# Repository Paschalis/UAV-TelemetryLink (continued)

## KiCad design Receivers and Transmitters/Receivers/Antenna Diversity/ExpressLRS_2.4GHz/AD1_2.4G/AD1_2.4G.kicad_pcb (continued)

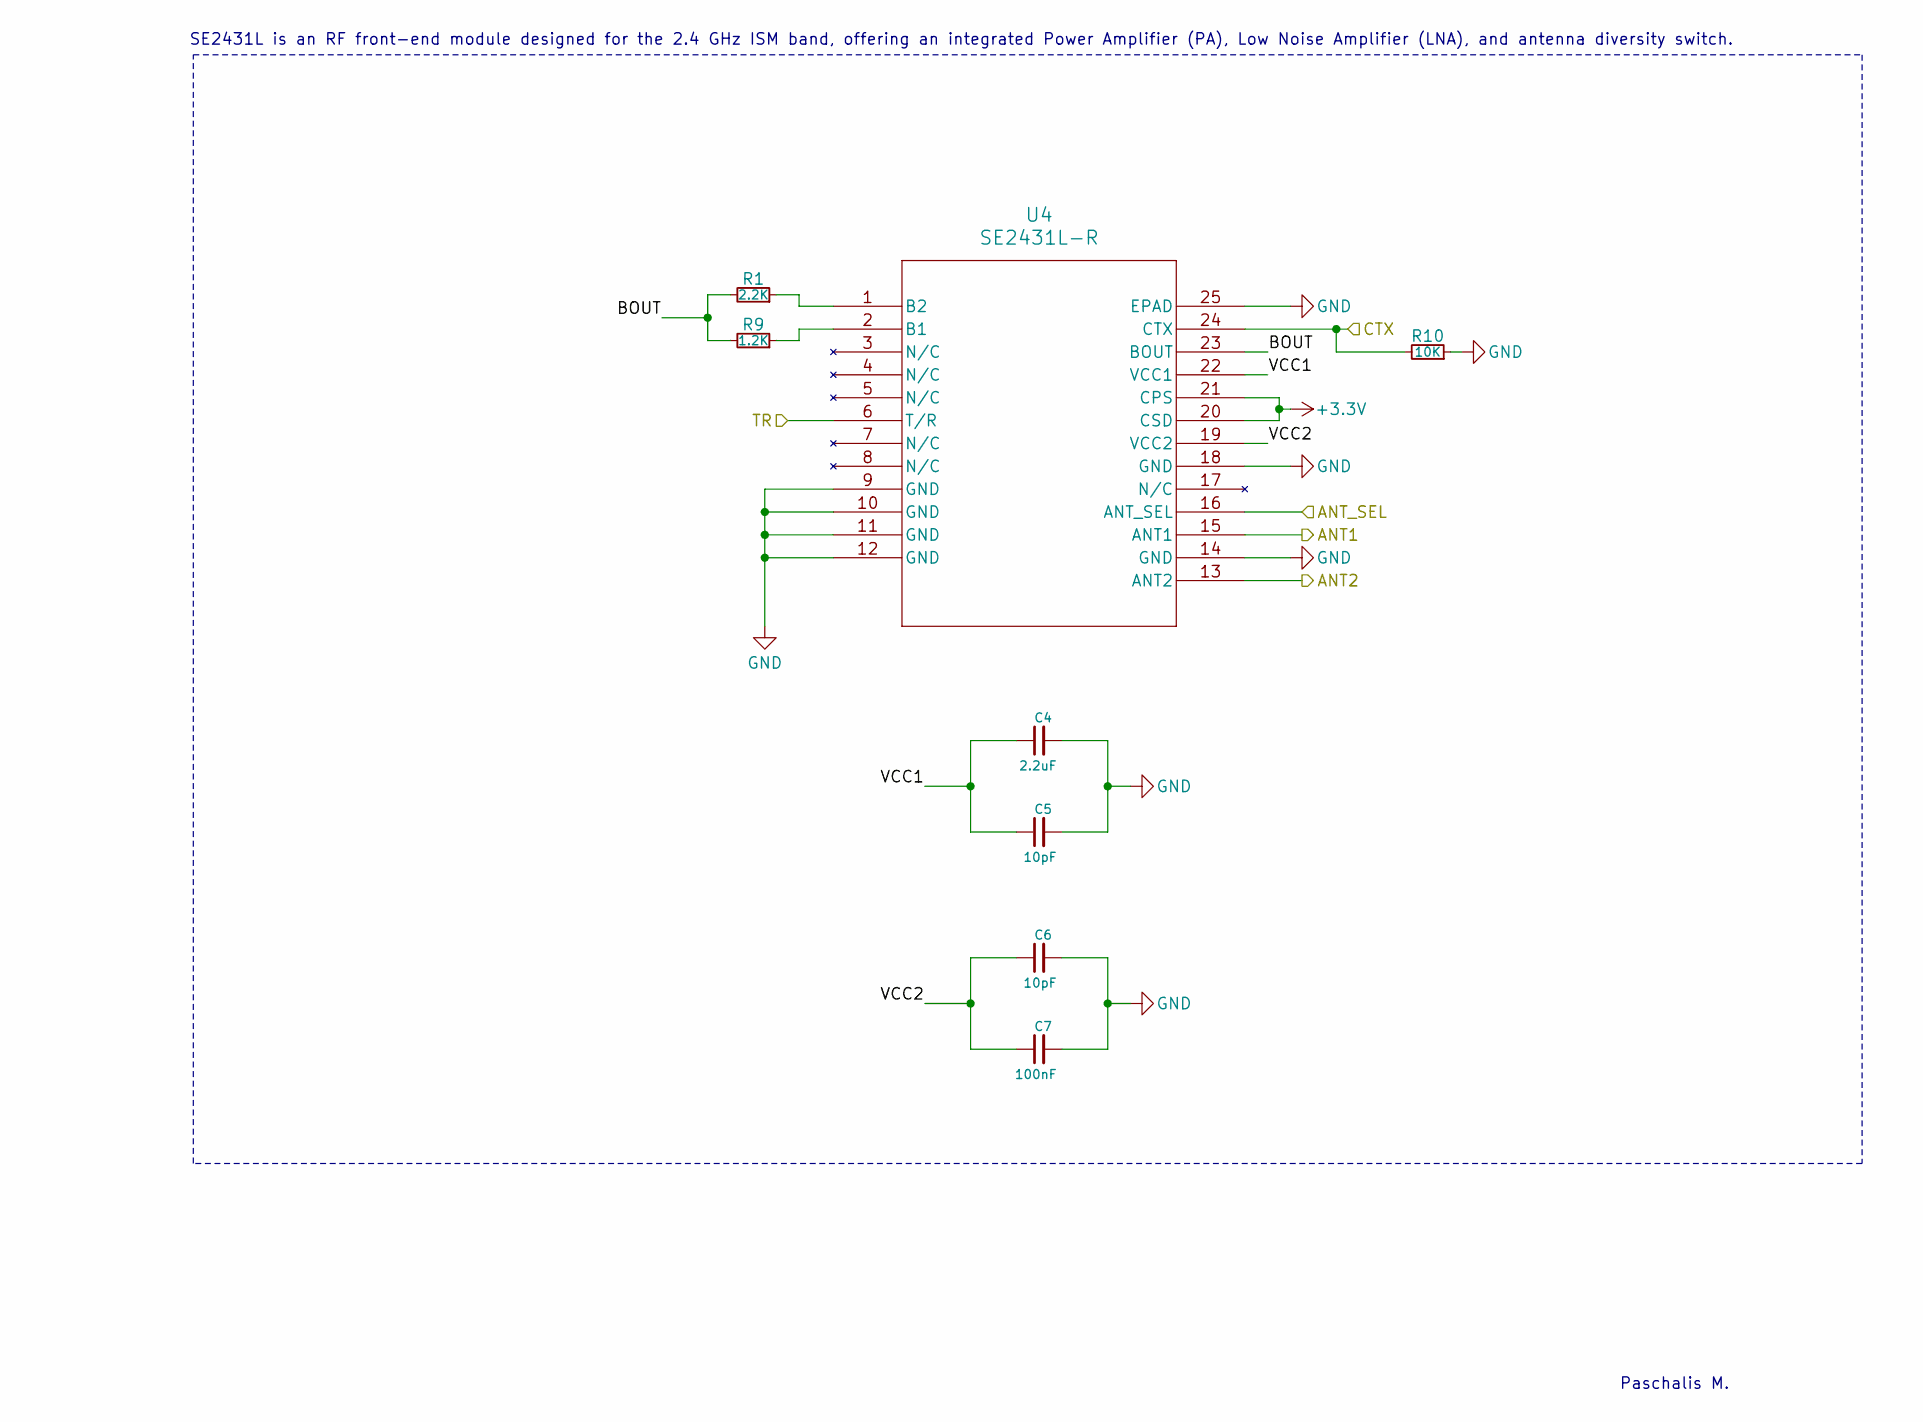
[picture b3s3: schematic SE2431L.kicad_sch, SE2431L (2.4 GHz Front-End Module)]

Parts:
C4: 2.2uF; C_0603_1608Metric_Pad1.08x0.95mm_HandSolder
C5, C6: 10pF; C_0603_1608Metric_Pad1.08x0.95mm_HandSolder
C7: 100nF; C_0603_1608Metric_Pad1.08x0.95mm_HandSolder
R1: 2.2K; R_0603_1608Metric_Pad0.98x0.95mm_HandSolder
R9: 1.2K; R_0603_1608Metric_Pad0.98x0.95mm_HandSolder
R10: 10K; R_0603_1608Metric_Pad0.98x0.95mm_HandSolder
U4: SE2431L-R; SE2431L_SKY

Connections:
+3.3V: U4.20 (CSD), U4.21 (CPS); also elsewhere on the board
/ESP8285/ANT_SEL: U4.16 (ANT_SEL); also elsewhere on the board
/ESP8285/CTX: R10.2, U4.24 (CTX); also elsewhere on the board
/SE2431L/ANT1: U4.15 (ANT1); also elsewhere on the board
/SE2431L/ANT2: U4.13 (ANT2); also elsewhere on the board
/SE2431L/BOUT: R1.2, R9.2, U4.23 (BOUT)
/SE2431L/TR: U4.6 (T/R); also elsewhere on the board
/SE2431L/VCC1: C4.1, C5.1, U4.22 (VCC1)
/SE2431L/VCC2: C6.1, C7.1, U4.19 (VCC2)
GND: C4.2, C5.2, C6.2, C7.2, R10.1, U4.9 (GND), U4.10 (GND), U4.11 (GND), U4.12 (GND), U4.14 (GND), U4.18 (GND), U4.25 (EPAD); also elsewhere on the board
unnamed: R9.1, U4.2 (B1)
unnamed: R1.1, U4.1 (B2)

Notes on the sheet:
Paschalis M.
SE2431L is an RF front-end module designed for the 2.4 GHz ISM band, offering an integrated Power Amplifier (PA), Low Noise Amplifier (LNA), and antenna diversity switch.

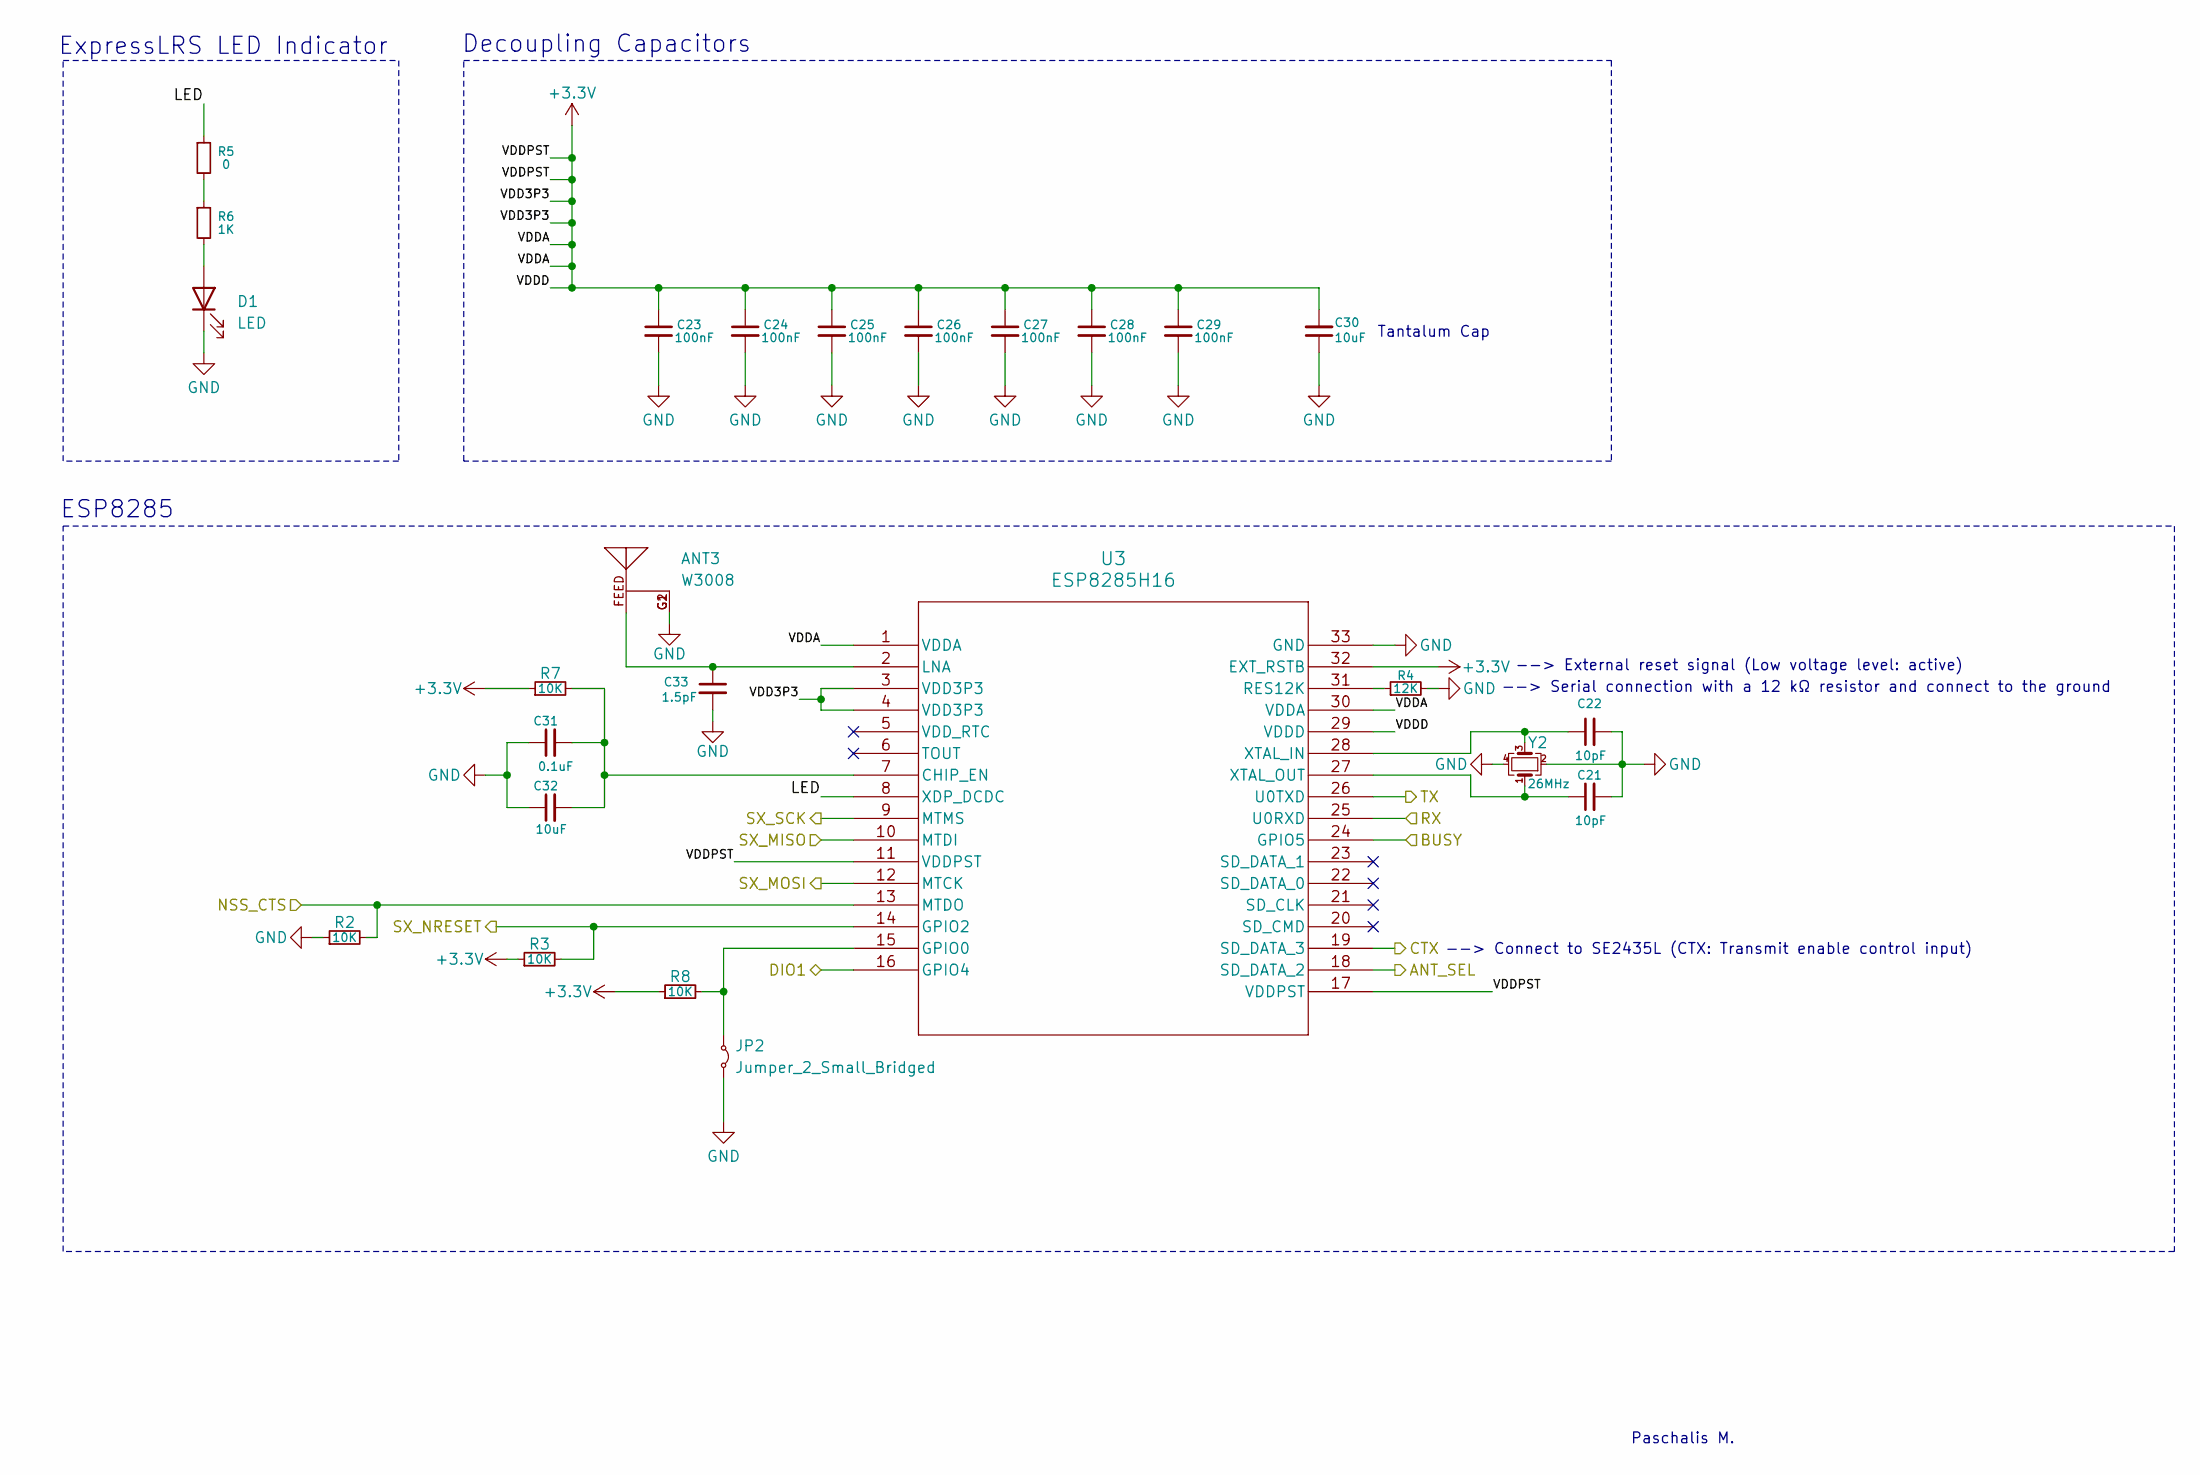
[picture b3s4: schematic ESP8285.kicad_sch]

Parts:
ANT3: W3008; ANTENNA_W3008
C21, C22: 10pF; C_0603_1608Metric_Pad1.08x0.95mm_HandSolder
C23, C24, C25, C26, C27, C28, C29: 100nF; C_0603_1608Metric_Pad1.08x0.95mm_HandSolder
C30, C32: 10uF; ECASD40J106M055K00
C31: 0.1uF; C_0603_1608Metric_Pad1.08x0.95mm_HandSolder
C33: 1.5pF; C_0402_1005Metric_Pad0.74x0.62mm_HandSolder
D1: LED; LED_0603_1608Metric_Pad1.05x0.95mm_HandSolder
JP2: Jumper_2_Small_Bridged; TestPoint_2Pads_Pitch2.54mm_Drill0.8mm
R2, R3, R7, R8: 10K; R_0603_1608Metric_Pad0.98x0.95mm_HandSolder
R4: 12K; R_0603_1608Metric_Pad0.98x0.95mm_HandSolder
R5: 0; R_0603_1608Metric_Pad0.98x0.95mm_HandSolder
R6: 1K; R_0603_1608Metric_Pad0.98x0.95mm_HandSolder
U3: ESP8285H16; QFN32_5X5_EXP
Y2: 26MHz; Crystal_SMD_2016-4Pin_2.0x1.6mm

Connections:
+3.3V: C23.1, C24.1, C25.1, C26.1, C27.1, C28.1, C29.1, C30.2, R3.1, R7.1, R8.1, U3.1 (VDDA), U3.3 (VDD3P3), U3.4 (VDD3P3), U3.11 (VDDPST), U3.17 (VDDPST), U3.29 (VDDD), U3.30 (VDDA), U3.32 (EXT_RSTB); also elsewhere on the board
/ESP8285/ANT_SEL: U3.18 (SD_DATA_2); also elsewhere on the board
/ESP8285/BUSY: U3.24 (GPIO5); also elsewhere on the board
/ESP8285/CTX: U3.19 (SD_DATA_3); also elsewhere on the board
/ESP8285/DIO1: U3.16 (GPIO4); also elsewhere on the board
/ESP8285/LED: R5.1, U3.8 (XDP_DCDC)
/ESP8285/NSS_CTS: R2.2, U3.13 (MTDO); also elsewhere on the board
/ESP8285/SX_MISO: U3.10 (MTDI); also elsewhere on the board
/ESP8285/SX_MOSI: U3.12 (MTCK); also elsewhere on the board
/ESP8285/SX_NRESET: R3.2, U3.14 (GPIO2); also elsewhere on the board
/ESP8285/SX_SCK: U3.9 (MTMS); also elsewhere on the board
/RX: U3.25 (U0RXD); also elsewhere on the board
/TX: U3.26 (U0TXD); also elsewhere on the board
GND: ANT3.G1, ANT3.G2, C21.2, C22.2, C23.2, C24.2, C25.2, C26.2, C27.2, C28.2, C29.2, C30.1, C31.1, C32.1, C33.2, D1.1 (K), JP2.2 (B), R2.1, R4.2, U3.33 (GND), Y2.2, Y2.4; also elsewhere on the board
unnamed: D1.2 (A), R6.2
unnamed: JP2.1 (A), R8.2, U3.15 (GPIO0)
unnamed: R5.2, R6.1
unnamed: C31.2, C32.2, R7.2, U3.7 (CHIP_EN)
unnamed: ANT3.FEED, C33.1, U3.2 (LNA)
unnamed: R4.1, U3.31 (RES12K)
unnamed: C22.1, U3.28 (XTAL_IN), Y2.3
unnamed: C21.1, U3.27 (XTAL_OUT), Y2.1

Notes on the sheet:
--> Serial connection with a 12 kΩ resistor and connect to the ground
--> External reset signal (Low voltage level: active)
Decoupling Capacitors
ExpressLRS LED Indicator
Tantalum Cap
Paschalis M.
--> Connect to SE2435L (CTX: Transmit enable control input)
ESP8285

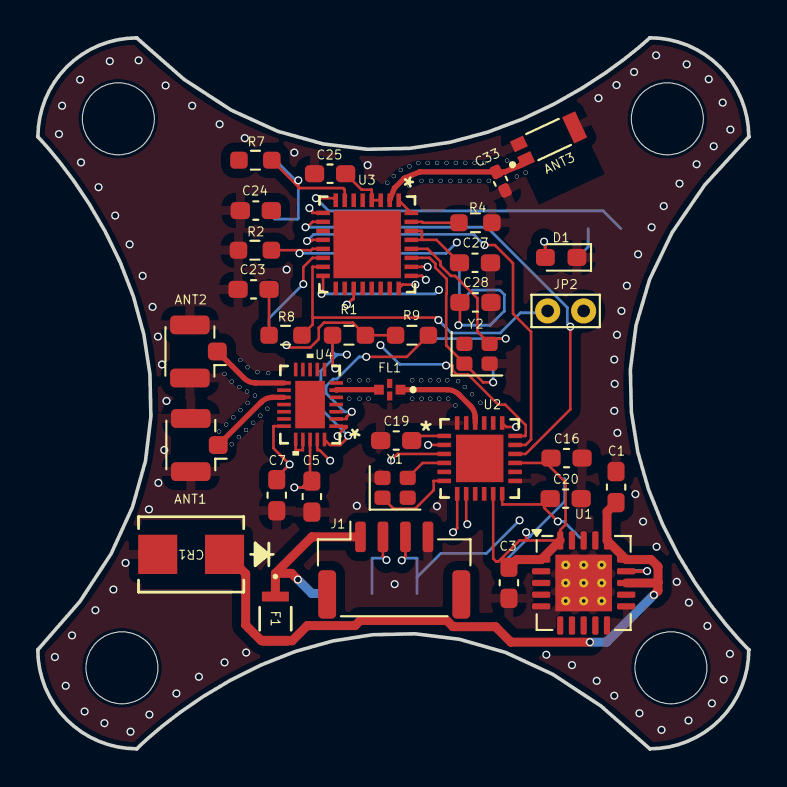
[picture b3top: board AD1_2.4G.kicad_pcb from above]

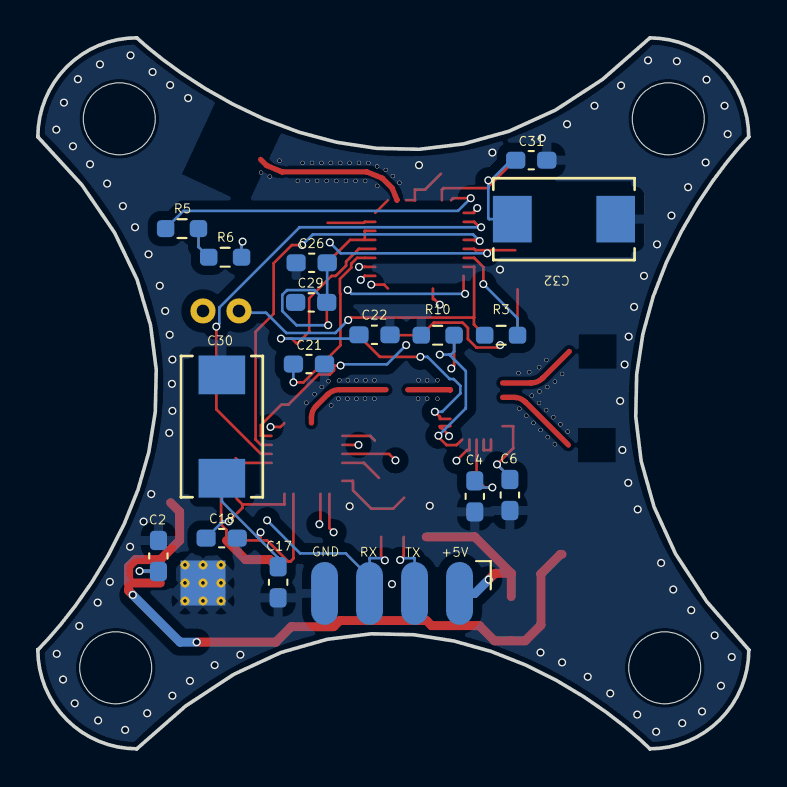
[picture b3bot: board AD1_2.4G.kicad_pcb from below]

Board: 6 copper layers, 39.5 x 39.5 mm, 55 parts (17 on the bottom side), 38 nets.

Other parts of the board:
hole1, hole4: MountingHole_4mm
hole2, hole3: (no value)

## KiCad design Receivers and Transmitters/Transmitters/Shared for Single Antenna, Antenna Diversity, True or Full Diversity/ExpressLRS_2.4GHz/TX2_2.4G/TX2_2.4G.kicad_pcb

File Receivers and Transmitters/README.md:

# Transmission Modes Classification

This document describes various transmission modes used in long-range LoRa (Long Range) wireless communication for drones. These modes leverage LoRa's unique capabilities to improve Signal Quality (LQ), mitigate interference, and enhance reliability over extended distances, making them ideal for drone applications in diverse environments.

## Transmission Modes

### 1. Single Antenna
- **Description**:  
  Uses one antenna on both the transmitter and receiver, operating over a single frequency channel.
- **Advantages**:  
  - Simplicity  
  - Low cost  
- **Limitations**:  
  - Highly susceptible to interference and signal loss.  

### 2. Antenna Diversity
- **Description**:  
  The receiver employs two antennas to select the best signal, while the transmitter uses a single antenna. Communication occurs over a single frequency channel.  
- **Advantages**:  
  - Improved signal quality due to antenna selection.  
- **Limitations**:  
  - Only one frequency channel is used.  
  - Transmission lacks diversity.  

### 3. True Diversity or Full Diversity
- **Description**:  
  Both the transmitter and receiver utilize two independent Semtech LoRa chips, each connected to its own antenna, operating on the same frequency. This setup provides full diversity for both transmitting and receiving.  
- **Advantages**:  
  - Enhanced signal quality through full transmitter and receiver diversity.  
  - Redundancy in signal transmission and reception.  
- **Limitations**:  
  - Increased complexity and cost.  

### 4. Gemini Mode (Single Band)
- **Description**:  
  The transmitter sends packets on two frequencies within the same band (e.g., 2.4 GHz or 900 MHz), spaced approximately 40 MHz apart for 2.4 GHz and 10 MHz apart for 900 MHz. A true diversity receiver with two antennas and LoRa chips receives both signals simultaneously.  
- **Advantages**:  
  - Superior interference mitigation by utilizing two frequencies within the same band.  
  - Improved stability and reliability of signal quality.  
- **Limitations**:  
  - Limited to a single frequency band.  

### 5. Gemini Xrossband GemX (Dual Band)
- **Description**:  
  The transmitter operates simultaneously on two different frequency bands (e.g., 2.4 GHz and 900 MHz), each managed by independent LoRa chips. The receiver employs true diversity hardware with two antennas and LoRa chips operating on distinct bands.  
- **Advantages**:  
  - Enhanced interference avoidance by operating across separate bands.  
  - Increased performance and redundancy for long-range communication.  
- **Limitations**:  
  - More complex and expensive hardware due to dual-band operation.  

## Transmission Mode Classification Chart

| Mode                        | Frequency Channels      | Antennas (TX) | Antennas (RX)| Interference Mitigation | Signal Quality  | Receiver Type        |
|-----------------------------|-------------------------|---------------|---------------|-------------------------|-----------------|----------------------|
| **Single Antenna**          | 1                      | 1             | 1             | Low                     | Low             | Simple Receiver      |
| **Antenna Diversity**       | 1                      | 1             | 2             | Moderate                | Moderate        | Diversity Receiver   |
| **True Diversity or Full Diversity**  | 1                      | 1             | 2             | High                    | High            | Diversity Receiver   |
| **Gemini Mode (Single Band)**| 2 (within 1 band)     | 2        | 2             | Very High               | Very High       | Diversity Receiver   |
| **Gemini Xrossband GemX (Dual Band)** | 2 (across 2 bands)     | 2             | 2                | Excellent               | Excellent       | Dual-band Receiver   |

## Summary

This classification illustrates the progression from basic single antenna setups to advanced true diversity and dual-band configurations:

- **Single Antenna** and **Antenna Diversity** provide fundamental solutions suitable for simple environments.  
- **True Diversity** or **Full Diversity** and **Gemini Mode (Single Band)** offer significant enhancements in reliability and interference mitigation within the same band.  
- **Gemini Xrossband GemX (Dual Band)** delivers optimal performance by leveraging dual-band communication, ideal for complex and interference-prone environments.  

Understanding these modes enables the selection of appropriate communication systems tailored to specific drone operation requirements, ensuring robust and efficient wireless links.

## Mounting and Enclosure Options

For practical deployment of the transmission systems described above, especially those involving Moxon or omnidirectional antennas operating at 2.4 GHz and 900 MHz, refer to the [TX_Enclosures_RC_Mounts](/Receivers%20and%20Transmitters/Transmitters/TX_Enclosures_RC_Mounts/) folder.

This directory contains 3D-printable enclosures and RC controller mounting designs for various transmitter boards. These mounts are optimized for signal performance, mechanical stability, and operator ergonomics across all transmission modes, from single antenna to Gemini Xrossband setups.

---

## References

- [mLRS GitHub Repository](https://github.com/olliw42/mLRS)  
- [mLRS Documentation](https://github.com/olliw42/mLRS-docu)  
- [mLRS Hardware Repository](https://github.com/olliw42/mLRS-hardware/tree/master)  
- [ArduPilot: mLRS RC Overview](https://ardupilot.org/copter/docs/common-mlrs-rc.html)  
- [ExpressLRS: Gemini Overview](https://www.expresslrs.org/software/gemini/)  
- [ExpressLRS Documentation](https://www.expresslrs.org/)  

[⬅️ Go Back to Main README](../README.md)

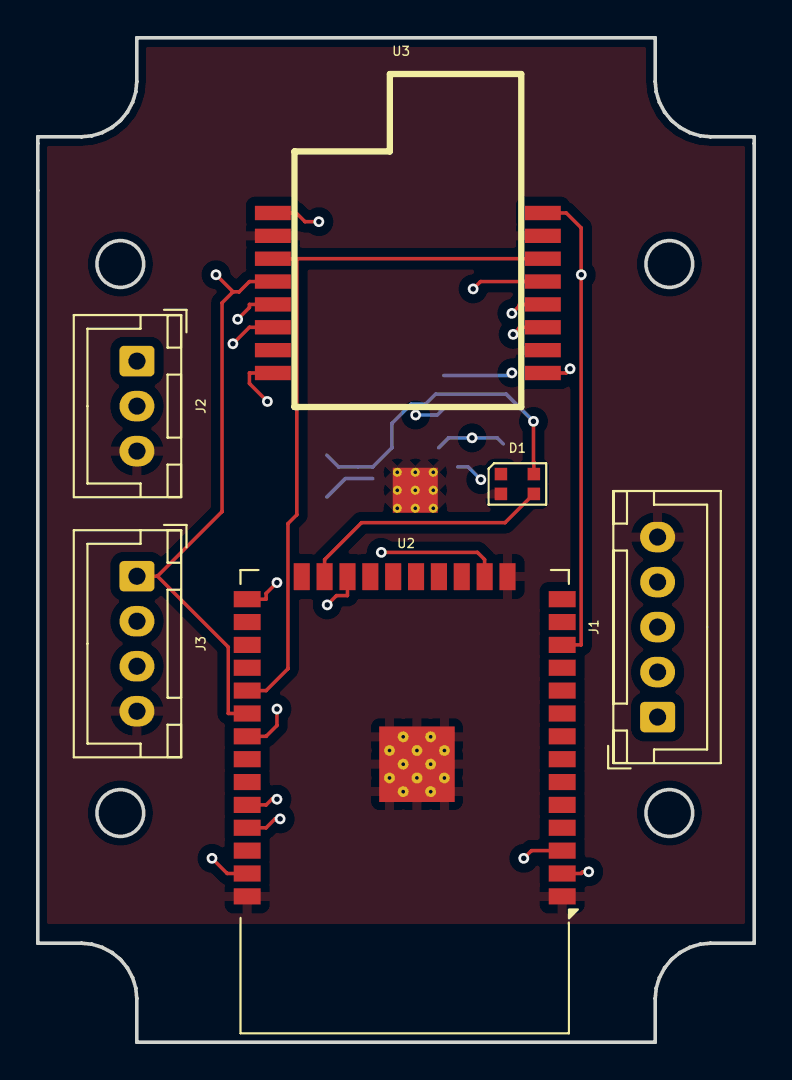
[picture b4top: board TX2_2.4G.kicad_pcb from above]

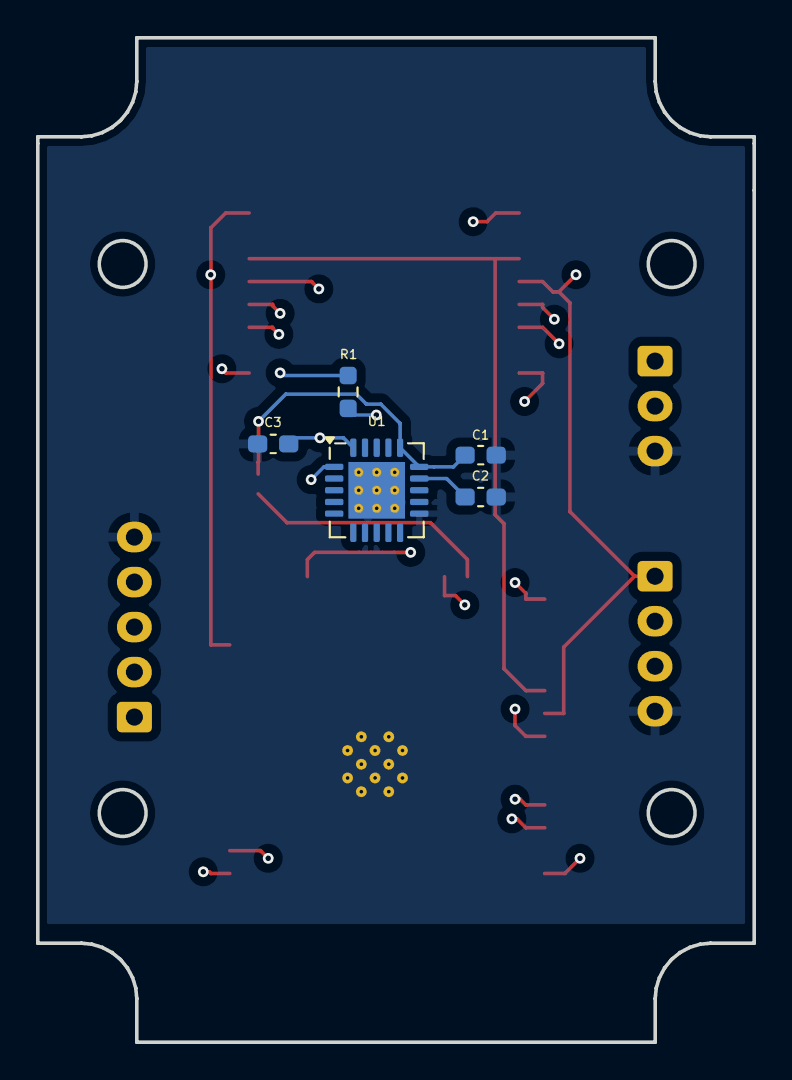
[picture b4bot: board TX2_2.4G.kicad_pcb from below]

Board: 4 copper layers, 39.8 x 55.8 mm, 11 parts (5 on the bottom side), 16 nets.

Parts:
C1: 10uF; C_0603_1608Metric_Pad1.08x0.95mm_HandSolder
C2: 1uF; C_0603_1608Metric_Pad1.08x0.95mm_HandSolder
C3: 47uF; C_0603_1608Metric_Pad1.08x0.95mm_HandSolder
D1: WS2812B-2020; LED_WS2812B-2020_PLCC4_2.0x2.0mm
J1: Conn_01x05_Socket; JST_XH_B5B-XH-A_1x05_P2.50mm_Vertical
J2: Conn_01x03_Socket; JST_XH_B3B-XH-A_1x03_P2.50mm_Vertical
J3: Conn_01x04_Socket; JST_XH_B4B-XH-A_1x04_P2.50mm_Vertical
R1: 10K; R_0603_1608Metric_Pad0.98x0.95mm_HandSolder
U1: TPS7A4701xRGW; Texas_RGW0020A_VQFN-20-1EP_5x5mm_P0.65mm_EP3.15x3.15mm_Ther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
U2: ESP32-WROOM-32
U3: E28-2G4M27S; E28

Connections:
+3.3V: C3.1, J1.4, J2.2, J3.3, R1.1, U1.1 (OUT), U1.20 (OUT), U2.2 (VDD), U3.1 (VCC)
+5V: C1.1, D1.4 (VDD), U1.13 (EN), U1.15 (IN), U1.16 (IN)
/BOOT0: J1.1, U2.25 (IO0)
/LED_RGB: D1.3 (DIN), U2.23 (IO15)
/MISO: U2.31 (IO19), U3.3 (MISO_TX)
/MOSI: U2.37 (IO23), U3.4 (MOSI_RX)
/NSS: U2.29 (IO5), U3.6 (NSS_CTS)
/RX: J1.3, U2.34 (RXD0/IO3)
/RX_EN: U2.12 (IO27), U3.8 (RX_EN)
/SCK: J3.1, U2.30 (IO18), U3.5 (SCK_RTSN)
/SDA: J3.2, U2.22 (SDI/SD1)
/SPORT: J2.1, U2.16 (IO13)
/TX: J1.2, U2.35 (TXD0/IO1)
GND: C1.2, C2.2, C3.2, D1.2 (VSS), J1.5, J2.3, J3.4, U1.7 (GND), U1.8 (1.6V), U1.11 (0.2V), U1.12 (0.1V), U1.21 (EP), U2.1 (GND), U2.15 (GND), U2.38 (GND), U2.39 (GND), U3.2 (GND), U3.7 (GND)
unnamed: C2.1, U1.14 (NR)
unnamed: R1.2, U2.3 (EN)

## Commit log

2025-01-11 Added README detailing transmission modes: Single Antenna, Antenna Diversity, True Diversity, Gemini Mode, and Gemini Xrossband GemX.
2025-01-11 Added "Go Back to Main README" button at the bottom of Receivers and Transmitters README
2025-01-12 Added .gitignore for KiCad PCB project to exclude temporary and exported files
2025-01-16 Added KiCad project files for the AD1_2.4GHz Antenna Diversity RX board.
2025-01-26 Remove small arrow from 'Receiver' in diversity.png
2025-01-27 Added site files to docs for Custom RX/TX Board Designs overview
2025-01-27 Initial update: README structure, images, and licenses
2025-01-29 Added UAV Telemetry Link badge to README.md
2025-02-25 Added True Antenna Diversity receiver implementation
2025-02-25 Added the TD1_2.4G.mp4 video in docs/Videos and updated docs/index.html to embed the video on the site.
2025-02-25 Added TD1_2.4G Entry to README
2025-03-15 Add new images and background video for documentation
2025-03-15 Update True Antenna Diversity TD1_2.4G KiCad schematics and PCB design
2025-03-15 Update README.md with latest TX/RX board details
2025-03-16 Add Hardware Setup image and Related Projects section in README
2025-03-16 Update Hardware Setup image: removed alpha channel and set white background
2025-03-16 Update Hardware Setup image: increased border margins
2025-03-18 Added BOM and updated README, removed obsolete KiCad files
2025-03-30 Updated hardware setup image, README, and KiCad project files for TX1_2.4G
2025-03-30 Added new images and TX2_2.4G project files
2025-03-30 Added TX board images and file links in README under 'TX Boards (Shared for Single Antenna, Antenna Diversity & True Diversity)' section
2025-03-31 Updated links in README files, modified hardware setup image, and added TX3_2.4G assets (images & videos).
2025-03-31 Fixed Markdown syntax for TX3 preview link
2025-04-06 Modified hardware setup image
2025-04-09 Updated GCS.png: added second drone and changed drone colors
2025-04-10 Updated schematics for TD1_2.4G receiver: ESP32, SX1280, and RFX2401C blocks
2025-04-10 Fixed alpha transparency in TX3.png
2025-04-12 Add Gemini Mode (Single Band) TX board files and PCB preview video (G_TX1.mp4)
2025-04-13 Add Gemini Mode (Single Band) TX board image and documentation updates - Updated hardware setup to include Gemini TX - Added G_TX1_2.4G preview image - Updated KiCad schematic with LNA section and 5.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
2025-04-13 Fixed incorrect LED RGB connection to ESP32 on TX2_2.4G and TX3_2.4G schematics and PCBs
2025-04-13 Update Gemini TX board video preview - Reflects updated PCB layout with LNA section - Includes 5.6pF matching capacitor for 50Ω impedance
2025-04-14 Fix URL spacing in Gemini Mode (Single Band) TX board preview link
2025-05-19 Add TX_Enclosures_RC_Mounts folder with 3D models and usage docs; linked in main README
2025-05-19 Uploaded V1.2 STL for Top_Bottom_Offset
    After physical verification, 3 more configurations will be uploaded.
2025-08-14 Update Antenna Diversity (AD1_2.4G), True Antenna Diversity (TD1_2.4G), and Gemini Mode transmitter (G_TX1): Modify KiCad files, add BOMs and production files; update images, docs, videos, and README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
2025-08-15 Update IBOM files with renamed HTML outputs and refresh images, KiCad project, README, and docs
2025-08-15 Update docs/index.html with adjusted IBOM file paths for GitHub Pages
2025-08-27 Update G_TX1 Freecad for enclosure and KiCad files (schematics, PCB, and project) - added fan pin headers
2025-09-10 Update AD1_2.4G: schematic revisions, project file, and README
2025-09-10 Update TD1_2.4G: schematic and PCB revisions, BOM export, README; remove old PCBWay production files
2025-09-10 Update G_TX1: PCB layout, project file, schematic, and README
